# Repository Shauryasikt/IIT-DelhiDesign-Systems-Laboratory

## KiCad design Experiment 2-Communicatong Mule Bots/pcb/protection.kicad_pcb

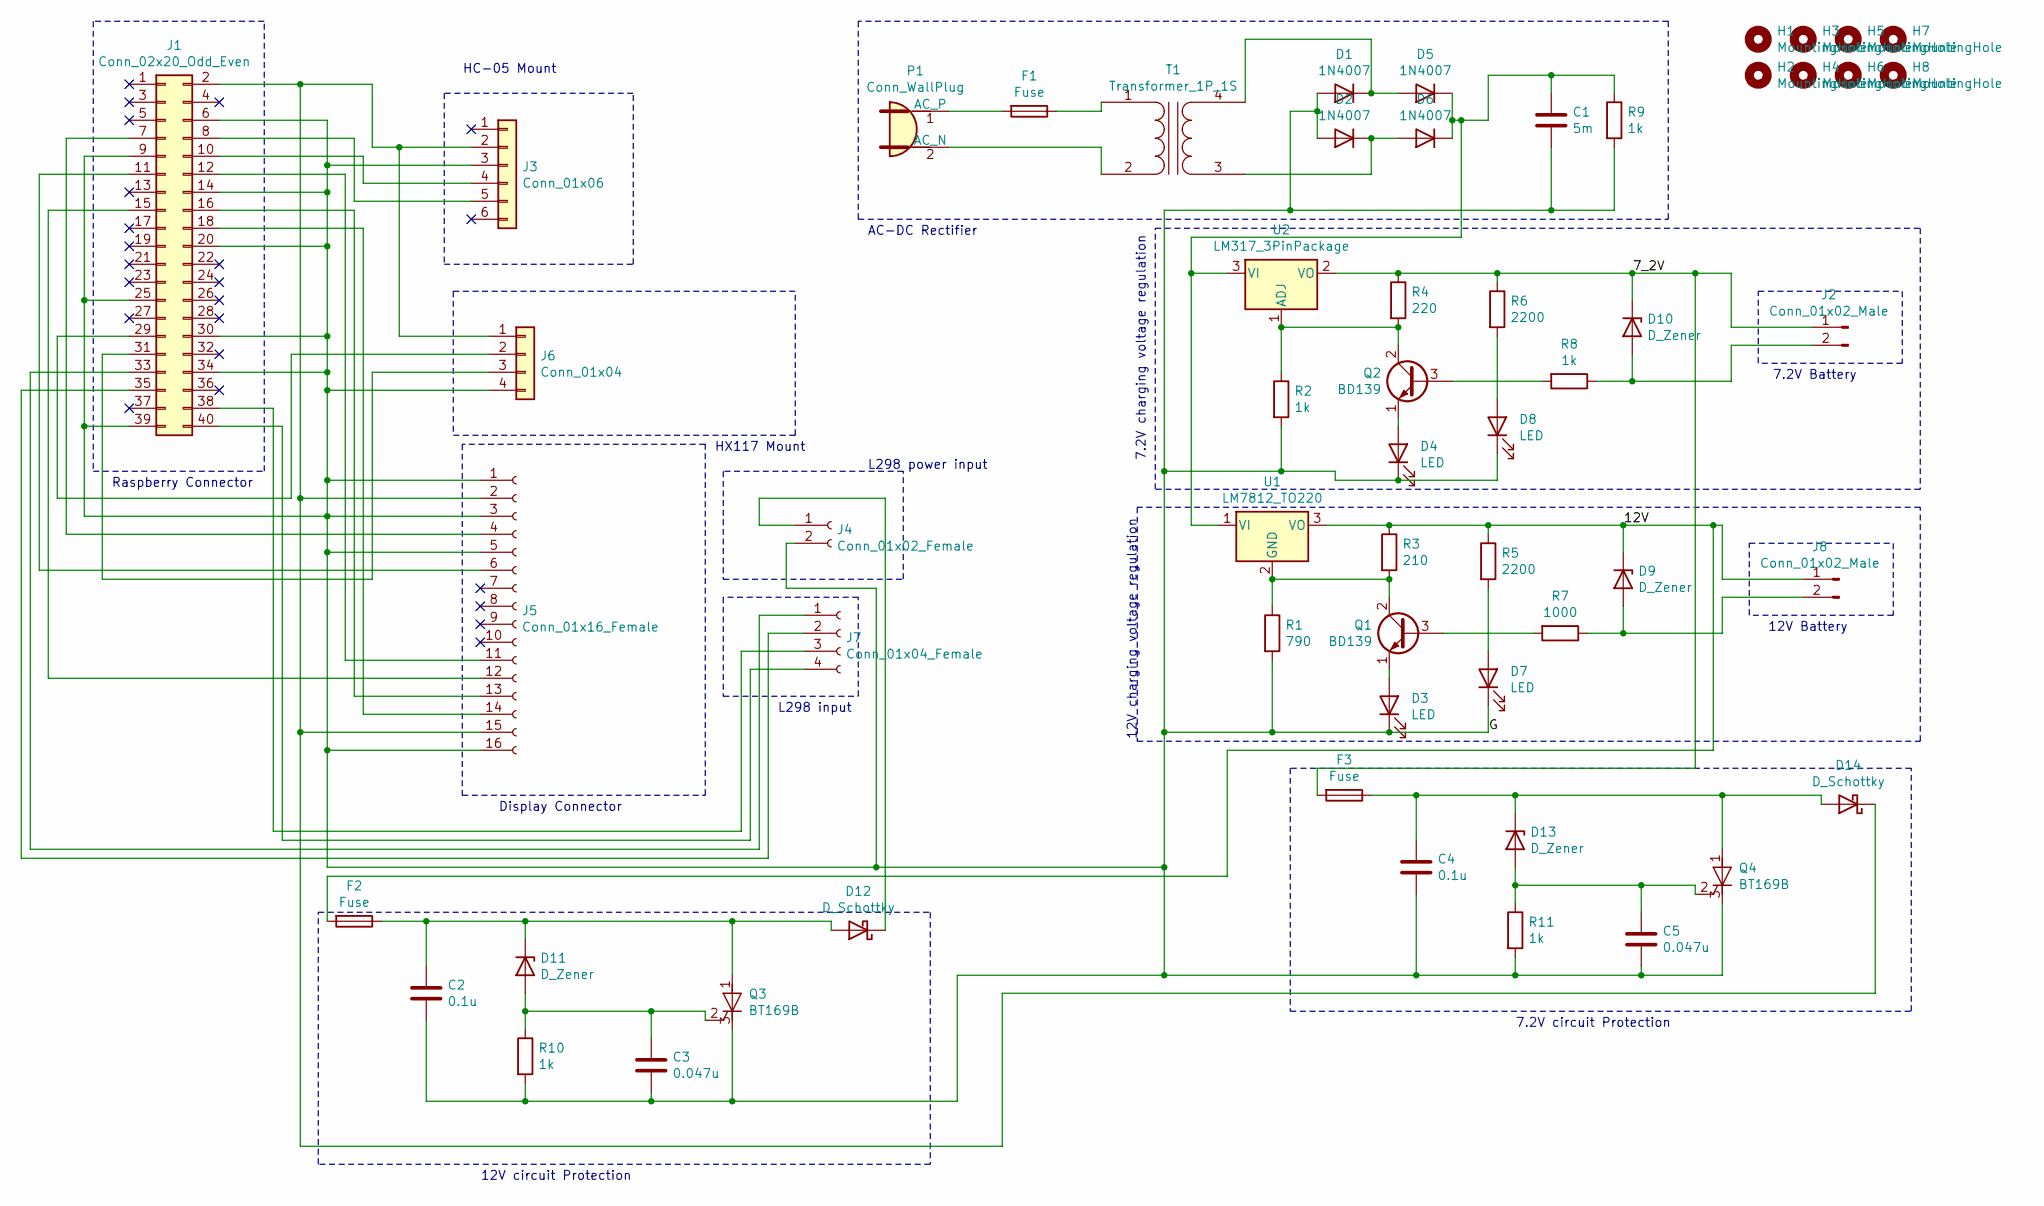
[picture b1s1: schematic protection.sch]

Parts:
C1: 5m; CP_Radial_D18.0mm_P7.50mm
C2, C4: 0.1u; C_1210_3225Metric
C3, C5: 0.047u; C_0805_2012Metric
D1, D2, D5, D6: 1N4007; D_DO-41_SOD81_P10.16mm_Horizontal
D3, D4, D7, D8: LED; LED_0603_1608Metric
D9, D11: D_Zener; D_1206_3216Metric
D10, D13: D_Zener; D_0603_1608Metric
D12, D14: D_Schottky; D_0805_2012Metric
F1, F2, F3: Fuse; Fuseholder_Cylinder-5x20mm_Bulgin_FX0457_Horizontal_Closed
H1, H2, H3, H4, H5, H6, H7, H8: MountingHole; MountingHole_2.1mm
J1: Conn_02x20_Odd_Even; PinHeader_2x20_P2.54mm_Vertical
J2, J8: Conn_01x02_Male; HANDSON_KF301-2P-back
J3: Conn_01x06; PinSocket_1x06_P2.54mm_Vertical
J4: Conn_01x02_Female; HANDSON_KF301-2P
J5: Conn_01x16_Female; PinSocket_1x16_P2.54mm_Vertical
J6: Conn_01x04; PinSocket_1x04_P2.54mm_Vertical
J7: Conn_01x04_Female; PinSocket_1x04_P2.54mm_Vertical
P1: Conn_WallPlug; HANDSON_KF301-2P
Q1, Q2: BD139; TO-126-3_Vertical
Q3, Q4: BT169B; TO-92_Inline
R1: 790; R_1206_3216Metric
R2, R8, R9, R10, R11: 1k; R_1206_3216Metric
R3: 210; R_1206_3216Metric
R4: 220; R_1206_3216Metric
R5, R6: 2200; R_0402_1005Metric
R7: 1000; R_1206_3216Metric
T1: Transformer_1P_1S; Transformer_37x44
U1: LM7812_TO220; TO-220-3_Vertical
U2: LM317_3PinPackage; TO-220-3_Vertical

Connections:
/7_2V: D10.1 (K), F3.2, J2.1, R4.1, R6.1, U2.2 (VO)
/12V: D9.1 (K), F2.2, J8.1, R3.1, R5.1, U1.3 (VO)
/G: C1.2, C2.2, C3.2, C4.2, C5.2, D1.2 (A), D2.2 (A), D3.1 (K), D4.1 (K), D7.1 (K), D8.1 (K), J1.6, J1.9, J1.14, J1.20, J1.25, J1.30, J1.34, J1.39, J3.3, J4.2, J5.1, J5.3, J5.5, J5.16, J6.4, Q3.3 (K), Q4.3 (K), R1.2, R2.2, R9.2, R10.2, R11.2
unnamed: C1.1, D5.1 (K), D6.1 (K), R9.1, U1.1 (VI), U2.3 (VI)
unnamed: C2.1, D11.1 (K), D12.2 (A), F2.1, Q3.1 (A)
unnamed: C3.1, D11.2 (A), Q3.2 (G), R10.1
unnamed: C4.1, D13.1 (K), D14.2 (A), F3.1, Q4.1 (A)
unnamed: C5.1, D13.2 (A), Q4.2 (G), R11.1
unnamed: D1.1 (K), D5.2 (A), T1.4 (SB)
unnamed: D2.1 (K), D6.2 (A), T1.3 (SA)
unnamed: D3.2 (A), Q1.1 (E)
unnamed: D4.2 (A), Q2.1 (E)
unnamed: D7.2 (A), R5.2
unnamed: D8.2 (A), R6.2
unnamed: D9.2 (A), J8.2, R7.1
unnamed: D10.2 (A), J2.2, R8.1
unnamed: D12.1 (K), J4.1
unnamed: D14.1 (K), J1.2, J3.2, J5.2, J5.15, J6.1
unnamed: F1.1, T1.1 (AA)
unnamed: F1.2, P1.1 (AC_P)
unnamed: J1.7, J5.4
unnamed: J1.8, J3.5
unnamed: J1.10, J3.4
unnamed: J1.11, J5.6
unnamed: J1.12, J5.11
unnamed: J1.15, J5.12
unnamed: J1.16, J5.13
unnamed: J1.18, J5.14
unnamed: J1.29, J6.2
unnamed: J1.31, J6.3
unnamed: J1.33, J7.1
unnamed: J1.35, J7.2
unnamed: J1.38, J7.3
unnamed: J1.40, J7.4
unnamed: P1.2 (AC_N), T1.2 (AB)
unnamed: Q1.2 (C), R1.1, R3.2, U1.2 (GND)
unnamed: Q1.3 (B), R7.2
unnamed: Q2.2 (C), R2.1, R4.2, U2.1 (ADJ)
unnamed: Q2.3 (B), R8.2

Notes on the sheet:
Raspberry Connector
Display Connector
HX117 Mount
HC-05 Mount
L298 input
AC-DC Rectifier
7.2V charging voltage regulation
7.2V circuit Protection
12V charging voltage regulation
12V circuit Protection
L298 power input
12V Battery
7.2V Battery

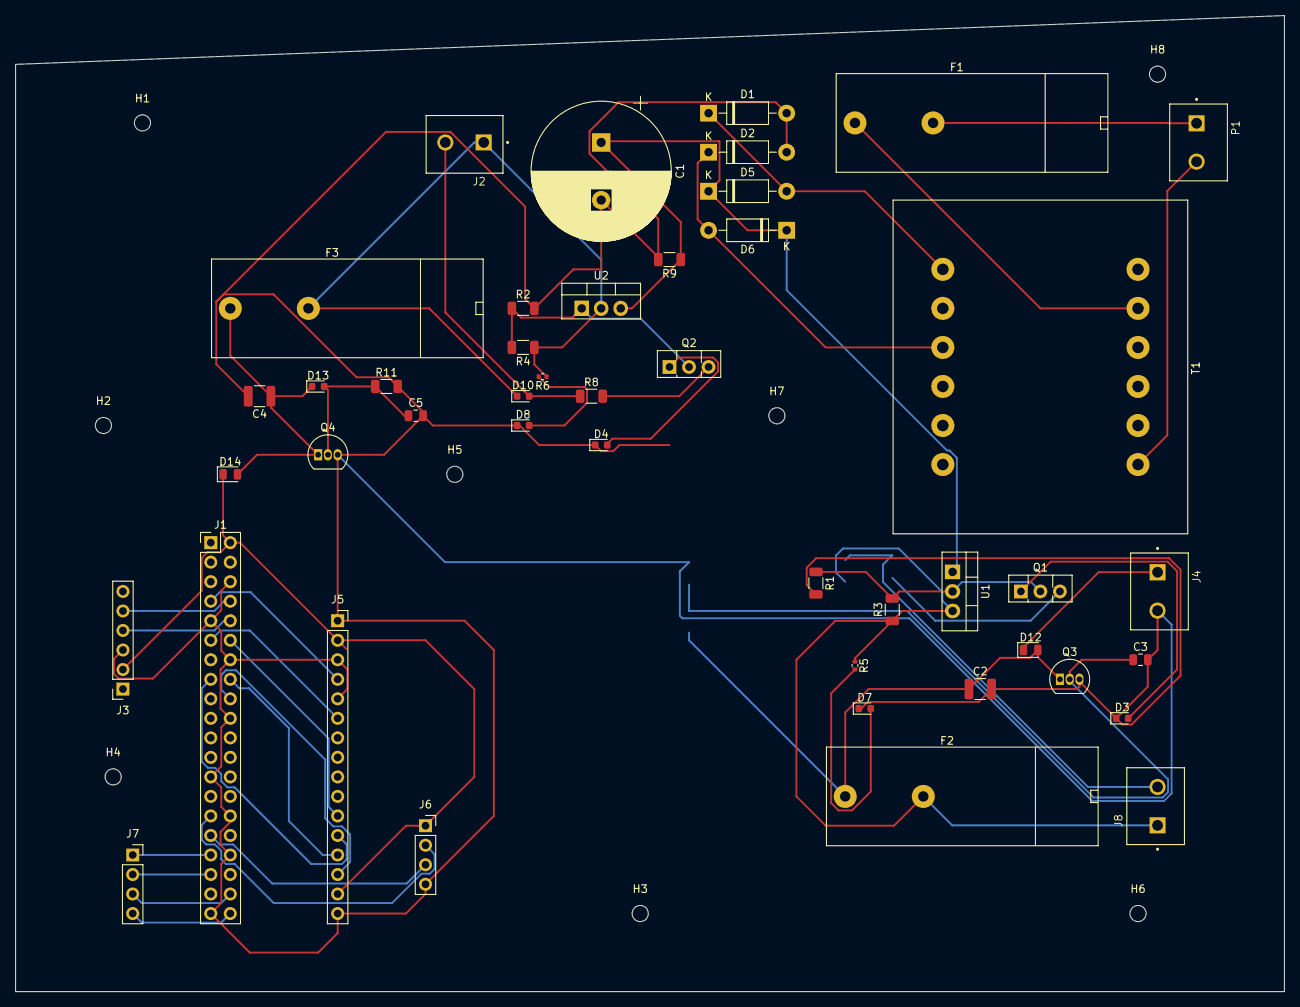
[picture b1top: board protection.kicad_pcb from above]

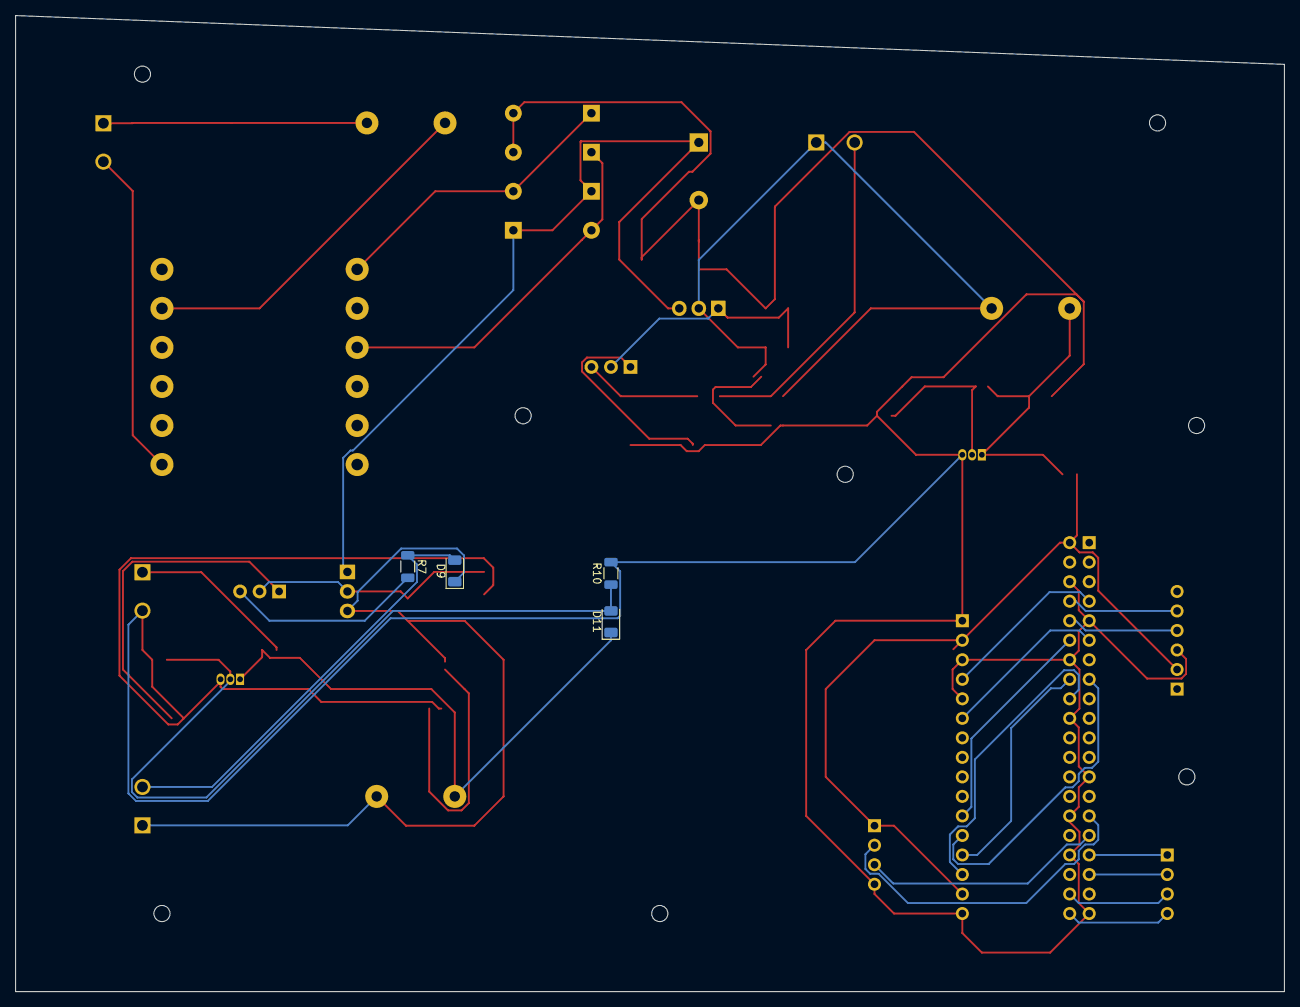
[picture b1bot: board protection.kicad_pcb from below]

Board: 2 copper layers, 165.1 x 127.0 mm, 57 parts (4 on the bottom side), 39 nets.

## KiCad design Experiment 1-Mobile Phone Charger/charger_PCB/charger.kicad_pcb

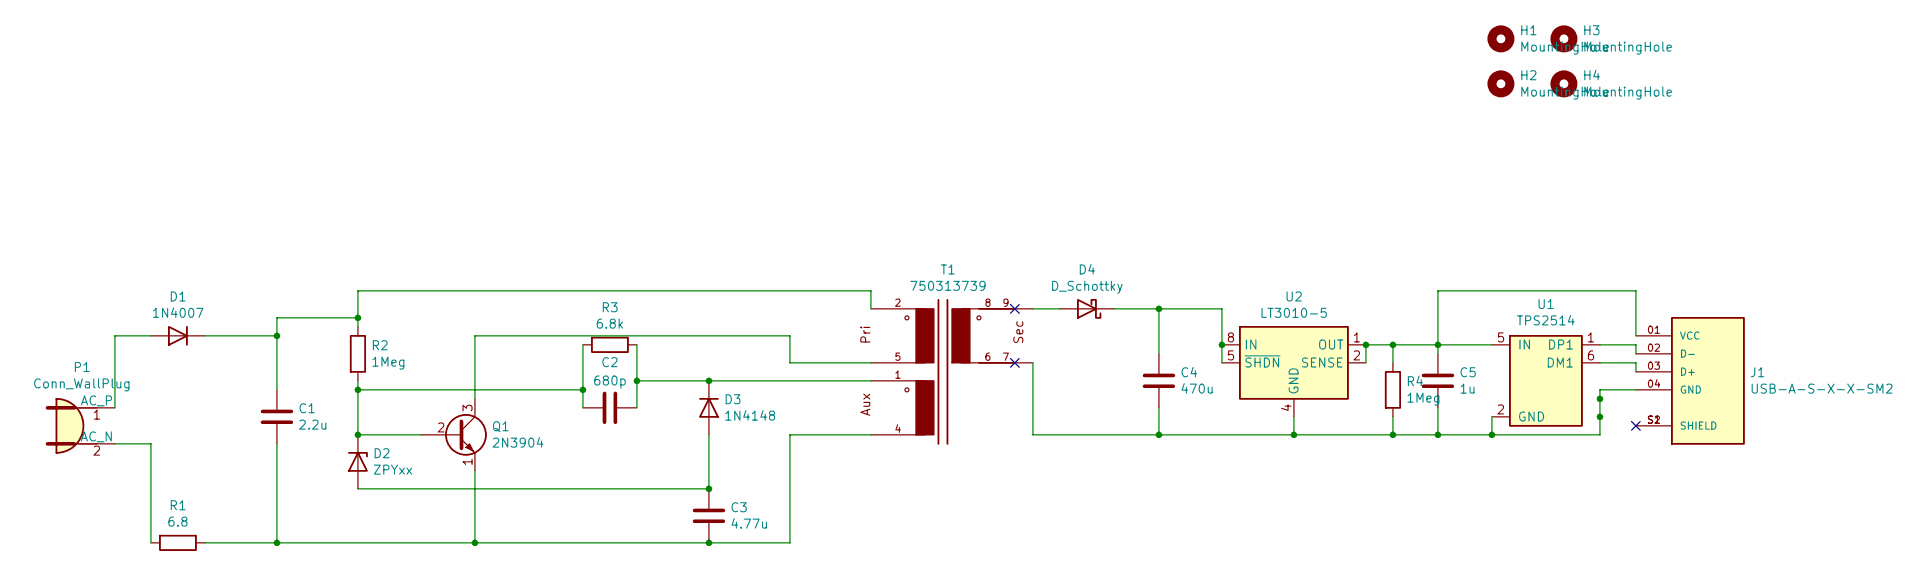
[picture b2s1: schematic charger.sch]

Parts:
C1: 2.2u; C_2225_5664Metric
C2: 680p; C_0805_2012Metric
C3: 4.77u; C_0603_1608Metric
C4: 470u; CAPC3216X100N
C5: 1u; CAPC3216X100N
D1: 1N4007; D_DO-41_SOD81_P10.16mm_Horizontal
D2: ZPYxx; D_DO-41_SOD81_P10.16mm_Horizontal
D3: 1N4148; D_DO-35_SOD27_P7.62mm_Horizontal
D4: D_Schottky; D_3220_8050Metric
H1, H2, H3, H4: MountingHole; MountingHole_2.2mm_M2_ISO7380
J1: USB-A-S-X-X-SM2; SAMTEC_USB-A-S-X-X-SM2; PARTREV T
P1: Conn_WallPlug; PinSocket_1x02_P2.54mm_Vertical
Q1: 2N3904; TO-92_Inline
R1: 6.8; RESC6432X60N
R2: 1Meg; R_1206_3216Metric
R3: 6.8k; R_0402_1005Metric
R4: 1Meg; R_1020_2550Metric
T1: 750313739; 5_THT_H_9PIN_EXT_(5280)
U1: TPS2514; SOT-23-6
U2: LT3010-5; MSOP-8-1EP_3x3mm_P0.65mm_EP1.68x1.88mm

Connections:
unnamed: C1.1, D1.1 (K), R2.1, T1.2
unnamed: C1.2, C3.2, Q1.1 (E), R1.1, T1.4
unnamed: C2.1, D2.1 (K), Q1.2 (B), R2.2, R3.2
unnamed: C2.2, D3.1 (K), R3.1, T1.1
unnamed: C3.1, D2.2 (A), D3.2 (A)
unnamed: C4.1, D4.1 (K), U2.5 (~SHDN), U2.8 (IN)
unnamed: C4.2, C5.2, J1.04 (GND), R4.2, T1.7, U1.2 (GND), U1.3 (NC), U1.4 (NC), U2.4 (GND), U2.9 (GND)
unnamed: C5.1, J1.01 (VCC), R4.1, U1.5 (IN), U2.1 (OUT), U2.2 (SENSE)
unnamed: D1.2 (A), P1.1 (AC_P)
unnamed: D4.2 (A), T1.9
unnamed: J1.02 (D-), U1.1 (DP1)
unnamed: J1.03 (D+), U1.6 (DM1)
unnamed: J1.S1 (SHIELD), J1.S2 (SHIELD)
unnamed: P1.2 (AC_N), R1.2
unnamed: Q1.3 (C), T1.5

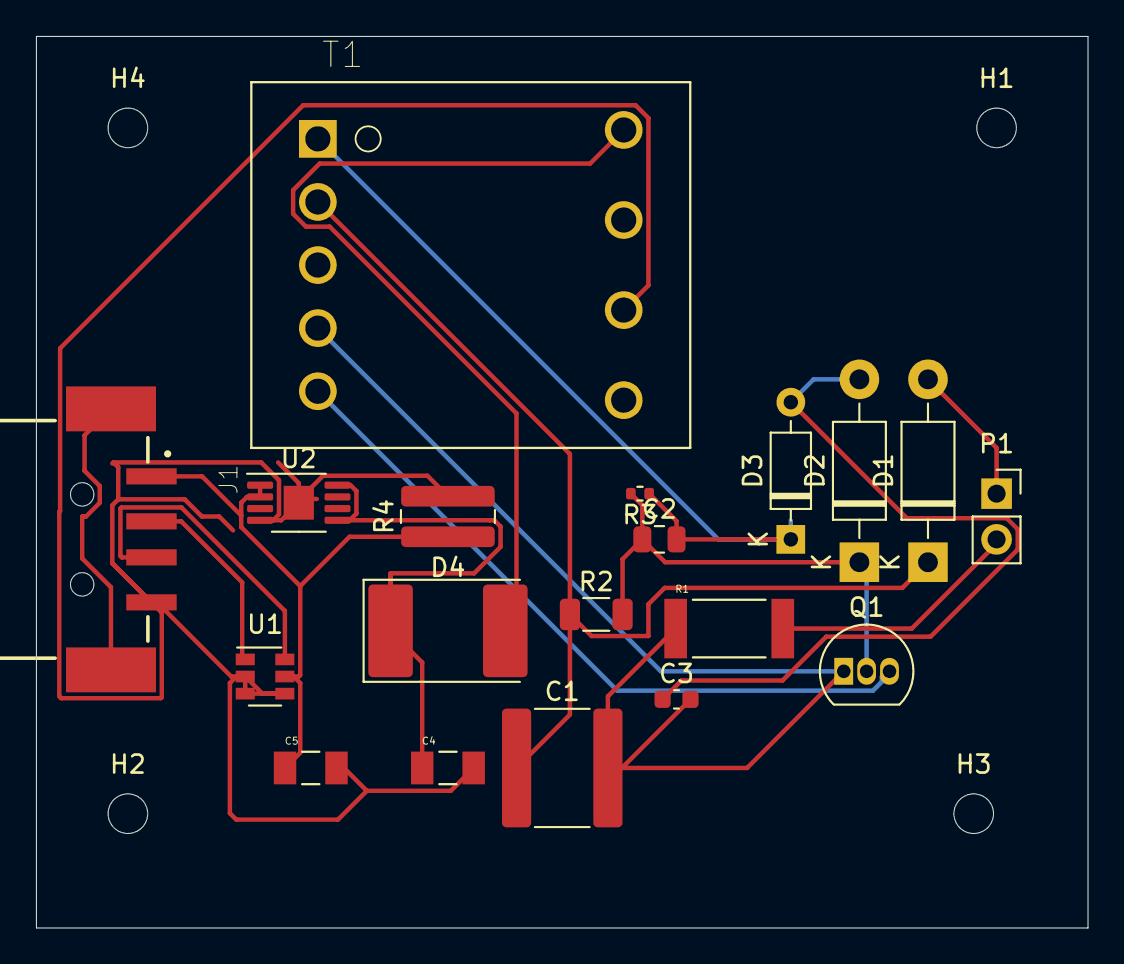
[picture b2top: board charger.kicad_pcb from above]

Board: 2 copper layers, 58.4 x 49.5 mm, 23 parts (0 on the bottom side), 15 nets.

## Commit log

2024-06-16 Rename ELP305 Exp 3.pdf to ELP305 Exp 3.pdf
